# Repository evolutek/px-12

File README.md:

# PX-12
The goal of this project is to control 5V pump and EV (such as https://fr.aliexpress.com/item/32792085658.html) via Dynamixel AX-12 protocol (Serial Half-duplex one wire), in order to reduce the number of cable inside the robot for Eurobot by daisy chaining the pump.
## Electronics
The PCB is solder directly at the end of the pump. A connector is present in order to connect the EV on the PCB. 

MCU: STM32F042G4\
Current shunt monitor: INA139
R_SHUNT: 0.01 Ohm

## Develloping on the PCB
In order to dev on the MCU you can use either STM32CubeIDE (Eclipse based) or VSCode.
### With VSCode
To dev STM32 chip with VSCode you need to install **stm-helper** from the extension manager in VSCode. After that you can either clone this repo and click on UpdateWorkspace, make sure 
to have the makefile and the .ioc in the source file tree otherwise the extension will not appear at the bottom of the app. Then you can click on **Build** to compile the project and **Download** to flash the MCU.
### Flashing the PCB 
Flashing is done via SWD port in the top of the PCB, in order to flash those PCB you'll need a STLINK V2. 

## TODO
* Add version V1.1 with vaccum sensor to replace the current shunt sensor. 
* Create software for the PX-12.
* Add documentation 
* Add exemple to work with arduino and STM32 platform

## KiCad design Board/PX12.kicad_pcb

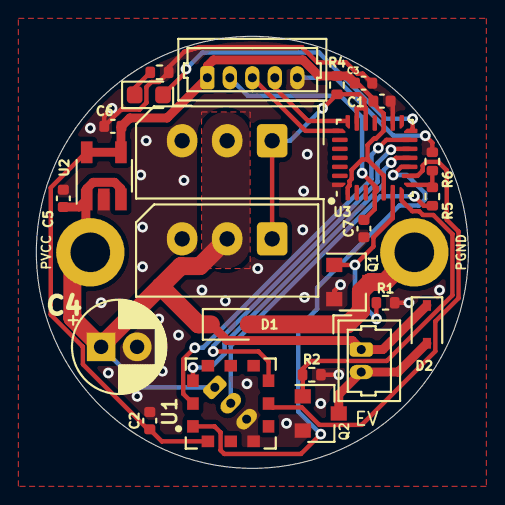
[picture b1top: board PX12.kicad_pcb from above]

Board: 2 copper layers, 24.0 x 24.0 mm, 28 parts (0 on the bottom side), 20 nets.

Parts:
AX12_1, AX12_2: Conn_01x03_Male; Molex_SPOX_5267-03A_1x03_P2.50mm_Vertical
C1, C2, C7: 100nF; C_0402_1005Metric
C3: 10µF; C_0402_1005Metric
C4: 33uF; CP_Radial_D5.0mm_P2.00mm
C5, C6: 1µF; C_0402_1005Metric
D1, D2: 1N4148W; D_SOD-323
D3: RED LED; LED_0603_1608Metric
PGND: MountingHole_Pad; MountingHole_2.2mm_M2_DIN965_Pad
PS1: Conn_01x03_Male; Molex_PicoBlade_53047-0310_1x03_P1.25mm_Vertical
PVCC: MountingHole_Pad; MountingHole_2.2mm_M2_DIN965_Pad
Q1, Q2: IRLML2060; SOT-23
R1, R2, R4: 10K; R_0402_1005Metric
R3: 560; R_0402_1005Metric
R5: R1; R_0402_1005Metric
R6: R2; R_0402_1005Metric
SWD1: Conn_01x05_Male; Molex_PicoBlade_53047-0510_1x05_P1.25mm_Vertical
U1: MPRLS0025PA00001A; XDCR_MPRLS0025PA00001A
U2: RT9078-33GJ5; TSOT-23-5
U3: STM32L031G6Ux; QFN-28_4x4mm_P0.5mm
VALVE1: Conn_01x02_Male; Molex_PicoBlade_53047-0210_1x02_P1.25mm_Vertical

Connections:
+3V3: C1.1, C2.1, C3.1, C6.1, R4.1, SWD1.1, U1.12, U2.4, U2.5, U3.1, U3.5, U3.17
/AX12: AX12_1.1, AX12_2.1, R4.2, U3.19, U3.20
/INT: U1.8, U3.9
/MISO: U1.7, U3.12
/MOSI: U1.2, U3.13
/PS: PS1.2, R5.1
/PUMP: Q1.1, R1.1, U3.6
/SCLK: U1.3, U3.11
/SWCLK: SWD1.3, U3.22
/SWDIO: SWD1.4, U3.21
/VALVE: Q2.1, R2.1, U3.7
/VALVE_GND: D2.2, Q2.3, VALVE1.2
/~RST: C7.1, SWD1.2, U3.4
/~SS: U1.1, U3.10
GND: AX12_1.3, AX12_2.3, C1.2, C2.2, C3.2, C4.2, C5.2, C6.2, C7.2, PS1.3, Q1.2, Q2.2, R1.2, R2.2, R3.1, R6.2, SWD1.5, U1.10, U2.2, U3.16, U3.28
unnamed: D1.2, PGND.1, Q1.3
unnamed: D3.1, R3.2
unnamed: D3.2, U3.14
unnamed: R5.2, R6.1, U3.8
VCC: AX12_1.2, AX12_2.2, C4.1, C5.1, D1.1, D2.1, PS1.1, PVCC.1, U2.1, U2.3, VALVE1.1

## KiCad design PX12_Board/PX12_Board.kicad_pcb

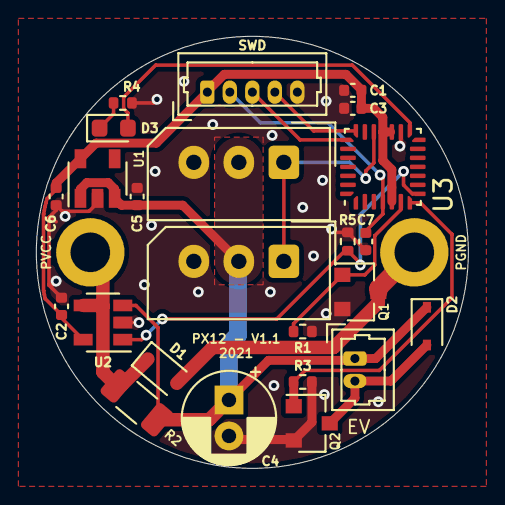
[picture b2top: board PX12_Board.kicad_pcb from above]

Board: 2 copper layers, 24.0 x 24.0 mm, 26 parts (0 on the bottom side), 15 nets.

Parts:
AX12_1, AX12_2: Conn_01x03_Male; Molex_SPOX_5267-03A_1x03_P2.50mm_Vertical
C1, C2, C7: 100nF; C_0402_1005Metric
C3: 10µF; C_0402_1005Metric
C4: 33µF; CP_Radial_D5.0mm_P2.00mm
C5, C6: 1µF; C_0402_1005Metric
D1, D2: BAV16WS-7-F; D_SOD-323
D3: LED; LED_0603_1608Metric
PGND: MountingHole_Pad; MountingHole_2.2mm_M2_DIN965_Pad
PVCC: MountingHole_Pad; MountingHole_2.2mm_M2_DIN965_Pad
Q1, Q2: IRLML2060; SOT-23
R1, R3: 10K; R_0402_1005Metric
R2: 0.01; R_1206_3216Metric
R4: 560; R_0402_1005Metric
R5: 3K; R_0402_1005Metric
SWD: Conn_01x05_Male; Molex_PicoBlade_53047-0510_1x05_P1.25mm_Vertical
U1: NCP718xSN330; SOT-23-5
U2: INA139; SOT-23-5
U3: STM32F042G4Ux; QFN-28_4x4mm_P0.5mm
VALVE1: Conn_01x02_Male; Molex_PicoBlade_53047-0210_1x02_P1.25mm_Vertical

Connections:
+3V3: C1.1, C2.1, C3.1, C6.1, SWD.1, U1.5, U2.5, U3.5, U3.17, U3.18
/P-: D1.1, PVCC.1, R2.2, U2.4
/PUMP_GND: D1.2, PGND.1, Q1.3
/VALVE_GND: D2.2, Q2.3, VALVE1.2
GND: AX12_1.3, AX12_2.3, C1.2, C2.2, C3.2, C4.2, C5.2, C6.2, C7.2, Q1.2, Q2.2, R1.2, R3.2, R4.2, R5.2, SWD.5, U1.2, U2.2, U3.16
unnamed: D3.1, R4.1
unnamed: D3.2, U3.15
Pump: Q1.1, R1.1, U3.6
RST: C7.1, SWD.2, U3.4
SERIAL: AX12_1.1, AX12_2.1, U3.19
SWCLK: SWD.3, U3.22
SWDIO: SWD.4, U3.21
VCC: AX12_1.2, AX12_2.2, C4.1, C5.1, D2.1, R2.1, U1.1, U1.3, U2.3, VALVE1.1
Va: R5.1, U2.1, U3.8
Valve: Q2.1, R3.1, U3.7

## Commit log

2020-11-22 Add gitignore generated from gitignore.io
2020-11-22 Add Schematic and pcb file for the pump PCB
2020-11-22 PCB routed, silkscreen done, need to review
2020-11-23 Connect pins on the MCU that were not connected
2020-11-23 Fix gitignore
2020-11-23 Interface doc create + pro
2020-11-23 Add 3D files
2020-11-23 Fix KLinPump PCB
2020-11-26 add panel
2020-11-29 New version of the PCB
2020-11-29 Replace previous name by current
2020-11-29 added OSHW logo on the back
2020-11-30 modify the connector pin
2020-12-07 Clean repos
2021-07-16 add stm32 doc
2021-07-16 first readme, to finish
2021-07-16 add todo
2021-07-16 Add interactive bom
2021-07-16 Add STM32 project
2021-07-18 vscode version + MCU at 48MHz and ADC files
2021-07-18 move 3D folder into kicad folder + 3d render of the pcb in doc
2021-07-18 New version of PCB V1.1
2021-07-18 Add AX12 documentation
2021-07-18 WIP ax12 code
2021-07-20 Add some methods to read and write eeprom/ram
2021-07-20 Split field enums in uint8 and uint16 type
2021-07-20 Add TODO, clean code
2021-07-20 Add instructions
2021-07-20 Write eeprom in flash
2021-07-20 Update PCB
2021-07-20 Reserve last flash memory page
2021-07-21 Add a checksum when flashing eeprom into flash
2021-07-22 [TEST] Echo on serial
2021-07-22 [TEST] Fix test
2021-12-07 Backup V1.0
2021-12-07 Add V2.0 board
